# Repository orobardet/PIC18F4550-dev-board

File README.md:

# PIC18F45(K)50 development and demo board

A development board for Microchip's 8 bits microcontroller [PIC18F4550](https://www.microchip.com/wwwproducts/en/PIC18F4550), compatible with [PIC18F45K50](https://www.microchip.com/wwwproducts/en/pic18f45k50).

**This is a work in progress**

## Features

- LCD
- RS232
- SPI temperature sensor
- I²C devices
  - LEDS
  - Buttons
  - ...
- TO COMPLETE
- ...

## BOM

TODO

## How to make

TODO

## Usage

TODO

## Software

TODO

## Pictures

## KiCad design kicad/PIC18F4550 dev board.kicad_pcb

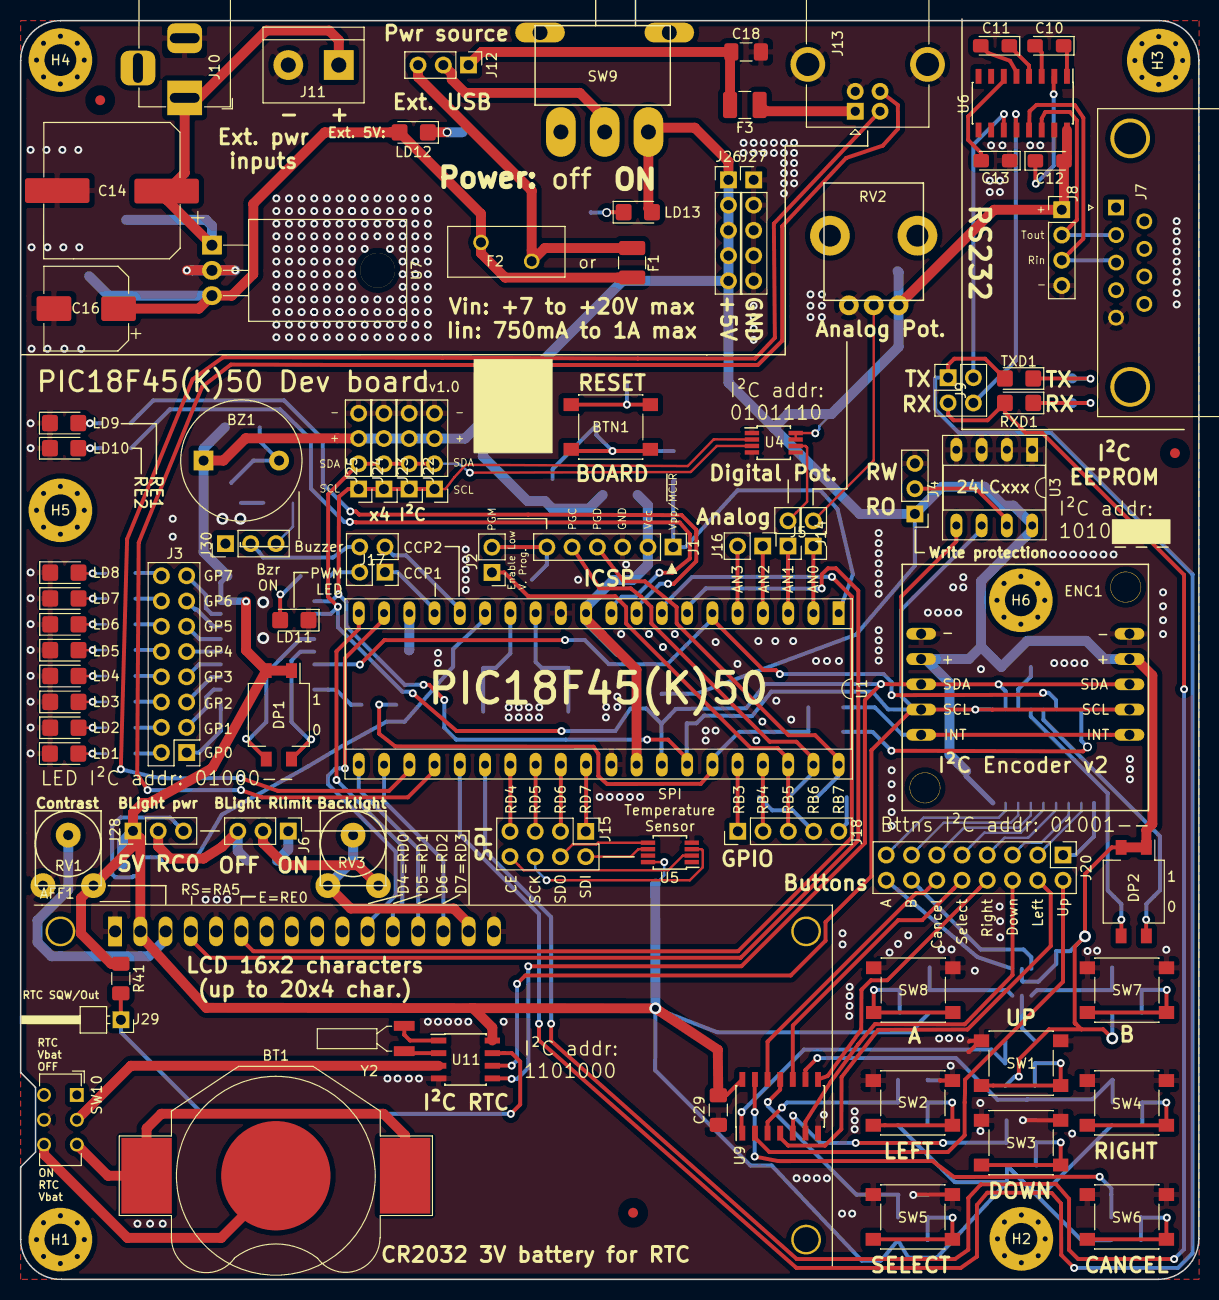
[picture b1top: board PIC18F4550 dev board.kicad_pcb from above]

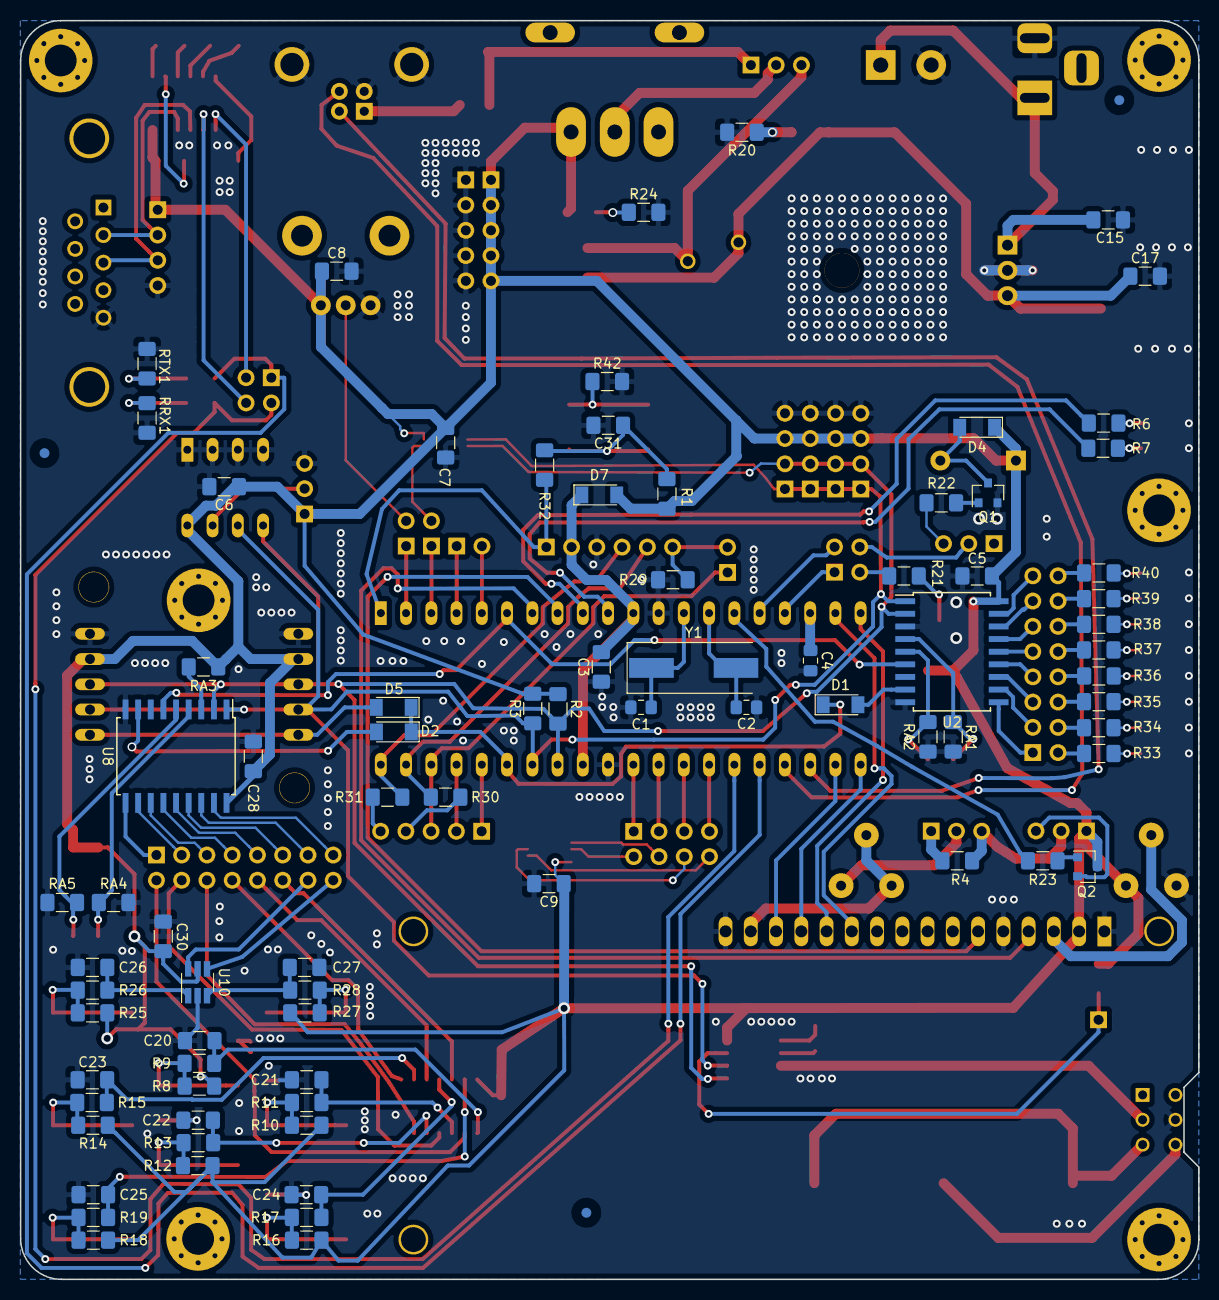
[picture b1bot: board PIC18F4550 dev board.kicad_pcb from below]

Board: 2 copper layers, 118.5 x 126.6 mm, 176 parts (83 on the bottom side), 156 nets.

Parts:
AFF1: WC1602A; WC1602A_NarrowPads
BT1: CR2032; BatteryHolder_Keystone_3002_1x20mm_SMD
BTN1: Reset; SW_SPST_PTS645
BZ1: Buzzer; Buzzer_12x9.5RM7.6
C1, C2: 15pF; C_0805_2012Metric_Pad1.15x1.40mm_HandSolder
C3, C5, C6, C7, C8, C9, C15, C17, C18, C28, C29, C30, C31: 100nF; C_1206_3216Metric_Pad1.42x1.75mm_HandSolder
C4: 330nF; C_0805_2012Metric_Pad1.15x1.40mm_HandSolder
C10, C11, C12, C13: 1µF; CP_EIA-3216-18_Kemet-A_Pad1.58x1.35mm_HandSolder
C14: 1000µF 25V; CP_Elec_12.50x13.5
C16: 470µF 16V; CP_Elec_8x10
C20, C21, C22, C23, C24, C25, C26, C27: 100nf; C_1206_3216Metric_Pad1.42x1.75mm_HandSolder
D1, D2, D5: LL4148; D_MiniMELF
D4, D7: BAS86; D_MiniMELF
DP1: LED addr; SW_DIP_SPSTx02_Slide_Omron_A6S-210x_W8.9mm_P2.54mm
DP2: Keys addr; SW_DIP_SPSTx02_Slide_Omron_A6S-210x_W8.9mm_P2.54mm
ENC1: I²C_Encoder_v2; I²C_Encoder_v2_THT_LongNarrowPads
F1: 750mA; Fuse_1210_3225Metric_Pad1.42x2.65mm_HandSolder
F2: 1A; Fuse_BelFuse_0ZRE0075FF_L11.5mm_W4.8mm
F3: 500mA; Fuse_1210_3225Metric_Pad1.42x2.65mm_HandSolder
FID1, FID2, FID3, FID4, FID5, FID6: Fiducial; Fiducial_1mm_Mask3mm
H1, H2, H3, H4, H5, H6: MountingHole; MountingHole_3.2mm_M3_Pad_Via
J1: ICSP; PinHeader_1x06_P2.54mm_Vertical
J2: LV Prog. EN; PinHeader_1x02_P2.54mm_Vertical
J3: LED GPIO; PinHeader_2x08_P2.54mm_Vertical
J4: Mem WP; THT_Sliding_Switch_PinHeader_2.54mm
J5: Digital pot; PinHeader_1x02_P2.54mm_Vertical
J6: LCD Rlimit; THT_Sliding_Switch_PinHeader_2.54mm
J7: DB9_Female; DSUB-9_Female_Horizontal_P2.77x2.84mm_EdgePinOffset7.70mm_H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
J8: RS232; PinHeader_1x04_P2.54mm_Vertical
J9: TX/RX; PinHeader_2x02_P2.54mm_Vertical
J10: Power IN jack; BarrelJack_Horizontal
J11: Power IN; TerminalBlock_bornier-2_P5.08mm
J12: Pwr Select; THT_Sliding_Switch_PinHeader_2.54mm
J13: USB_B; USB_B_OST_USB-B1HSxx_Horizontal
J14: AN0; PinHeader_1x02_P2.54mm_Vertical
J15: SPI; PinHeader_2x04_P2.54mm_Vertical
J16: Analog; PinHeader_1x02_P2.54mm_Vertical
J17: PWM; PinHeader_2x02_P2.54mm_Vertical
J18: I/O; PinHeader_1x05_P2.54mm_Vertical
J20: Buttons; PinHeader_2x08_P2.54mm_Vertical
J22: External I2C 1; PinHeader_1x04_P2.54mm_Vertical
J23: External I2C 2; PinHeader_1x04_P2.54mm_Vertical
J24: External I2C 3; PinHeader_1x04_P2.54mm_Vertical
J25: External I2C 4; PinHeader_1x04_P2.54mm_Vertical
J26: +5V; PinHeader_1x05_P2.54mm_Vertical
J27: GND; PinHeader_1x05_P2.54mm_Vertical
J28: LCD pwr.; THT_Sliding_Switch_PinHeader_2.54mm
J29: RTC Sqw/Out; PinHeader_1x01_P2.54mm_Horizontal
J30: Buzzer SW; THT_Sliding_Switch_PinHeader_2.54mm
LD1, LD2, LD3, LD4, LD5, LD6, LD7, LD8: Y; LED_1206_3216Metric_Castellated
LD9: R; LED_1206_3216Metric_Castellated
LD10, LD12: B; LED_1206_3216Metric_Castellated
LD11: W; LED_1206_3216Metric_Castellated
LD13: G; LED_1206_3216Metric_Castellated
Q1, Q2: BC817; SOT-23
R1, R2, R3, R22, R23, R32, R41: 4.7k; R_1206_3216Metric_Pad1.42x1.75mm_HandSolder
R4, R6, R7, R21, R33, R34, R35, R36, R37, R38, R39, R40: 470; R_1206_3216Metric_Pad1.42x1.75mm_HandSolder
R8, R10, R12, R14, R16, R18, R25, R27: 100k; R_1206_3216Metric_Pad1.42x1.75mm_HandSolder
R9, R11, R13, R15, R17, R19, R26, R28, R29, R30, R31: 10k; R_1206_3216Metric_Pad1.42x1.75mm_HandSolder
R20, R24: 1k; R_1206_3216Metric_Pad1.42x1.75mm_HandSolder
R42: 100; R_1206_3216Metric_Pad1.42x1.75mm_HandSolder
RA1, RA2, RA3, RA4, RA5: 10k; R_1206_3216Metric_Pad1.42x1.75mm_HandSolder
RRX1: 470; R_1206_3216Metric_Pad1.42x1.75mm_HandSolder
RTX1: 470; R_1206_3216Metric_Pad1.42x1.75mm_HandSolder
RV1: 10k; Trimming_pot_SR_Passives_RKT6V_5mm
RV2: 100k; PCB_Pot_SR_Passives_R9011
RV3: 470; Trimming_pot_SR_Passives_RKT6V_5mm
RXD1: Y; LED_1206_3216Metric_Castellated
SW1: Up; SW_SPST_PTS645
SW2: Left; SW_SPST_PTS645
SW3: Down; SW_SPST_PTS645
SW4: Right; SW_SPST_PTS645
SW5: Select; SW_SPST_PTS645
SW6: Back; SW_SPST_PTS645
SW7: B; SW_SPST_PTS645
SW8: A; SW_SPST_PTS645
SW9: Power; Angle_Sliding_Switch_4.4mmPitch
SW10: SW_DPDT_x2; SW_CuK_JS202011AQN_DPDT_Angled
TXD1: B; LED_1206_3216Metric_Castellated
U1: PIC18F4550-IP; DIP-40_W15.24mm_Socket_LongNarrowPads
U2, U8: MCP23008; SOIC-18W_7.5x11.6mm_P1.27mm
U3: 24LC16; DIP-8_W7.62mm_Socket_LongNarrowPads
U4: MCP4551; MSOP-8_3x3mm_P0.65mm
U5: TC72; MSOP-8_3x3mm_P0.65mm
U6: MAX232; SOIC-16_3.9x9.9mm_P1.27mm
U7: LM7805_TO220; TO-220-3_Horizontal_TabDown
U9: 74HC14; SOIC-14_3.9x8.7mm_P1.27mm
U10: 74LVC2G14; SOT-23-6_Handsoldering
U11: DS1307Z+; SOIC-8_3.9x4.9mm_P1.27mm
Y1: 20 MHz; Crystal_SMD_HC49-SD
Y2: 32.768kHz, 12.5pF; Crystal_Can_Diam2x6_SMD

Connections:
+5V: AFF1.2, BZ1.1, C5.1, C6.1, C7.1, C8.1, C9.1, C12.2, C28.1, C29.1, C30.1, D4.1, D7.2, DP1.1, DP1.2, DP2.1, DP2.2, ENC1.2, J4.1, J8.1, J22.3, J23.3, J24.3, J25.3, J26.1, J26.2, J26.3, J26.4, J26.5, J28.1, LD13.2, Q2.3, R1.1, R2.1, R3.1, R8.1, R10.1, R12.1, R14.1, R16.1, R18.1, R25.1, R27.1, R41.1, RA3.2, RV1.3, RV2.3, SW9.1, U2.18, U3.8, U4.7, U4.8, U5.8, U6.16, U8.18, U9.14, U10.5, U11.8
/I2C/B1: J20.2, U9.2
/I2C/B2: J20.4, U9.4
/I2C/B3: J20.6, U9.6
/I2C/B4: J20.8, U9.8
/I2C/B5: J20.10, U9.10
/I2C/B6: J20.12, U9.12
/I2C/B7: J20.14, U10.6
/I2C/B8: J20.16, U10.4
/MCU/RTCVbat: SW10.2, U11.3
/MCU/Vdd: C3.1, D7.1, J1.2, U1.11, U1.32
/Power/Vreg: F1.1, F2.1, J12.3
/UI/CE: J15.8, U5.2
/UI/SCK: J15.6, U5.3
/UI/SDI: J15.2, U5.6
/UI/SDO: J15.4, U5.5
AN0: J14.1, U1.2
AN1: J5.1, U1.3
AN2: J16.1, U1.4
AN3: J16.2, U1.5
CCP1: J17.1, U1.17
CCP2: J17.3, U1.16
D+: J13.3, U1.24
D-: J13.2, U1.23
GND: AFF1.1, AFF1.5, AFF1.16, C1.1, C2.1, C3.2, C4.2, C5.2, C6.2, C7.2, C8.2, C9.2, C13.1, C14.2, C15.2, C16.2, C17.2, C18.2, C20.2, C21.2, C22.2, C23.2, C24.2, C25.2, C26.2, C27.2, C28.2, C29.2, C30.2, C31.2, ENC1.1, J1.3, J4.3, J7.5, J8.4, J10.2, J11.2, J13.4, J13.5, J22.4, J23.4, J24.4, J25.4, J27.1, J27.2, J27.3, J27.4, J27.5, LD1.1, LD2.1, LD3.1, LD4.1, LD5.1, LD6.1, LD7.1, LD8.1, LD9.1, LD10.1, LD11.1, Q1.2, R20.2, R24.2, R29.2, R42.2, RA1.2, RA2.2, RA4.2, RA5.2, RRX1.2, RTX1.2, RV1.1, RV2.1, SW1.1, SW2.1, SW3.1, SW4.1, SW5.1, SW6.1, SW7.1, SW8.1, SW10.5, U1.12, U1.31, U2.3, U2.9, U3.1, U3.2, U3.3, U3.4, U4.1, U4.4, U4.5, U5.4, U6.15, U7.2, U8.9, U9.7, U10.2, U11.4
INT2: D1.1, D2.1, D5.1, U1.35
MCLR: J1.1, R32.2, U1.1
unnamed: AFF1.3, RV1.2
unnamed: AFF1.15, RV3.1, RV3.2
unnamed: BT1.1, SW10.3
unnamed: BT1.2, SW10.6
unnamed: BTN1.1, C31.1, R1.2, R32.1
unnamed: BTN1.2, R42.1
unnamed: BZ1.2, D4.2, Q1.3
unnamed: C10.1, U6.1
unnamed: C10.2, U6.3
unnamed: C11.1, U6.4
unnamed: C11.2, U6.5
unnamed: C12.1, U6.2
unnamed: C13.2, U6.6
unnamed: C14.1, C15.1, J10.1, J11.1, U7.1
unnamed: C16.1, C17.1, F1.2, F2.2, LD12.2, U7.3
unnamed: C20.1, R9.2, U9.1
unnamed: C21.1, R11.2, U9.3
unnamed: C22.1, R13.2, U9.5
unnamed: C23.1, R15.2, U9.9
unnamed: C24.1, R17.2, U9.11
unnamed: C25.1, R19.2, U9.13
unnamed: C26.1, R26.2, U10.1
unnamed: C27.1, R28.2, U10.3
unnamed: D1.2, U2.8
unnamed: D2.2, U8.8
unnamed: D5.2, ENC1.5
unnamed: DP1.3, RA1.1, U2.4
unnamed: DP1.4, RA2.1, U2.5
unnamed: DP2.3, RA4.1, U8.4
unnamed: DP2.4, RA5.1, U8.5
unnamed: F3.2, J13.1
unnamed: J1.6, J2.2, R29.1
unnamed: J3.1, U2.10
unnamed: J3.2, R33.2
unnamed: J3.3, U2.11
unnamed: J3.4, R34.2
unnamed: J3.5, U2.12
unnamed: J3.6, R35.2
unnamed: J3.7, U2.13
unnamed: J3.8, R36.2
unnamed: J3.9, U2.14
unnamed: J3.10, R37.2
unnamed: J3.11, U2.15
unnamed: J3.12, R38.2
unnamed: J3.13, U2.16
unnamed: J3.14, R39.2
unnamed: J3.15, U2.17
unnamed: J3.16, R40.2
unnamed: J4.2, U3.7
unnamed: J5.2, U4.6
unnamed: J6.1, R4.1
unnamed: J6.2, RV3.3
unnamed: J7.2, J8.2, U6.14
unnamed: J7.3, J8.3, U6.13
unnamed: J9.2, U6.11
unnamed: J9.4, U6.12
unnamed: J12.2, SW9.2
unnamed: J14.2, RV2.2
unnamed: J17.2, R21.2
unnamed: J17.4, J30.2
unnamed: J18.4, R30.1
unnamed: J18.5, R31.1
unnamed: J20.1, U8.10
unnamed: J20.3, U8.11
unnamed: J20.5, U8.12
unnamed: J20.7, U8.13
unnamed: J20.9, U8.14
unnamed: J20.11, U8.15
unnamed: J20.13, U8.16
unnamed: J20.15, U8.17
unnamed: J6.3, J28.2, R4.2
unnamed: J28.3, Q2.2
unnamed: J29.1, R41.2, U11.7
unnamed: J30.3, R22.2
unnamed: LD1.2, R33.1
unnamed: LD2.2, R34.1
unnamed: LD3.2, R35.1
unnamed: LD4.2, R36.1
unnamed: LD5.2, R37.1
unnamed: LD6.2, R38.1
unnamed: LD7.2, R39.1
unnamed: LD8.2, R40.1
unnamed: LD9.2, R6.2
unnamed: LD10.2, R7.2
unnamed: LD11.2, R21.1
unnamed: LD12.1, R20.1
unnamed: LD13.1, R24.1
unnamed: Q1.1, R22.1
unnamed: Q2.1, R23.2
unnamed: R8.2, R9.1, SW1.2
unnamed: R10.2, R11.1, SW2.2
unnamed: R12.2, R13.1, SW3.2
unnamed: R14.2, R15.1, SW4.2
unnamed: R16.2, R17.1, SW5.2
unnamed: R18.2, R19.1, SW6.2
unnamed: R25.2, R26.1, SW7.2
unnamed: R27.2, R28.1, SW8.2
unnamed: RA3.1, U8.3
unnamed: RRX1.1, RXD1.1
unnamed: RTX1.1, TXD1.1
unnamed: U11.1, Y2.2
unnamed: U11.2, Y2.1
OSC1: C1.2, U1.13, Y1.1
OSC2: C2.2, U1.14, Y1.2
RA4: U1.6, U2.6, U8.6
RA5: AFF1.4, U1.7
RB3: J18.1, U1.36
RB4: J18.2, U1.37
RB5: J2.1, J18.3, U1.38
RB6: J1.5, R30.2, U1.39
RB7: J1.4, R31.2, U1.40
RC0: R23.1, U1.15
RD0: AFF1.11, U1.19
RD1: AFF1.12, U1.20
RD2: AFF1.13, U1.21
RD3: AFF1.14, U1.22
RD4: J15.7, U1.27
RD5: J15.5, U1.28
RD6: J15.3, U1.29
RD7: J15.1, U1.30
RE0: AFF1.6, U1.8
RE1: R6.1, U1.9
RE2: R7.1, U1.10
RX: J9.3, RXD1.2, U1.26
SCL: ENC1.4, J22.1, J23.1, J24.1, J25.1, R3.2, U1.34, U2.1, U3.6, U4.2, U8.1, U11.6
SDA: ENC1.3, J22.2, J23.2, J24.2, J25.2, R2.2, U1.33, U2.2, U3.5, U4.3, U8.2, U11.5
TX: J9.1, TXD1.2, U1.25
VUSB: C4.1, U1.18
Vin_USB: C18.1, F3.1, J12.1

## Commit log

2019-04-20 Add MPLabX demo project
